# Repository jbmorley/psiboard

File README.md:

# PsiBoard

Psion Series 5 based bluetooth keyboard.

## BOM

### FFC Connector

https://www.digikey.com/en/products/detail/molex/0524372271/3262899

22 Position FFC, FPC Connector Contacts, Bottom 0.020" (0.50mm) Surface Mount, Right Angle

### Reset Switch

https://www.digikey.com/en/products/detail/panasonic-electronic-components/EVQ-P7A01P/4429447

## Development

### Useful Links

- [ZMK Firmware - List of Keycodes](https://zmk.dev/docs/keymaps/list-of-keycodes)
- [ZMK Firmware - Power Management Configuration](https://zmk.dev/docs/config/power)
- [Pro Micro Pinout](https://learn.sparkfun.com/tutorials/pro-micro--fio-v3-hookup-guide/all)

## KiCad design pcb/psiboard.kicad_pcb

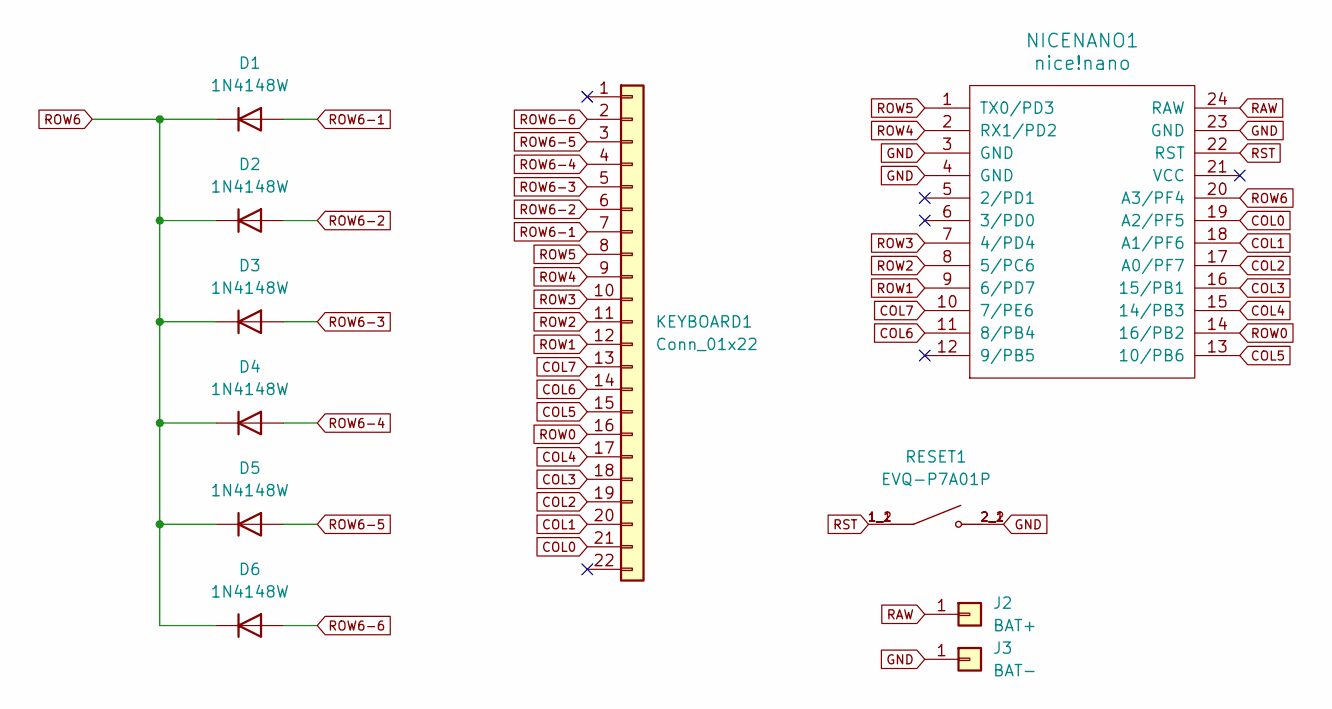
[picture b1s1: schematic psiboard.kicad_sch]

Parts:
D1, D2, D3, D4, D5, D6: 1N4148W; D_SOD-123
J2: BAT+; TestPoint_Pad_2.0x2.0mm
J3: BAT-; TestPoint_Pad_2.0x2.0mm
KEYBOARD1: Conn_01x22; CON_524372271_MOL
NICENANO1: nice!nano
RESET1: EVQ-P7A01P; SW_EVQ-P7A01P; PARTREV 2022.4

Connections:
COL0: KEYBOARD1.21, NICENANO1.19 (A2/PF5)
COL1: KEYBOARD1.20, NICENANO1.18 (A1/PF6)
COL2: KEYBOARD1.19, NICENANO1.17 (A0/PF7)
COL3: KEYBOARD1.18, NICENANO1.16 (15/PB1)
COL4: KEYBOARD1.17, NICENANO1.15 (14/PB3)
COL5: KEYBOARD1.15, NICENANO1.13 (10/PB6)
COL6: KEYBOARD1.14, NICENANO1.11 (8/PB4)
COL7: KEYBOARD1.13, NICENANO1.10 (7/PE6)
GND: J3.1, NICENANO1.3 (GND), NICENANO1.4 (GND), NICENANO1.23 (GND), RESET1.2_1, RESET1.2_2
RAW: J2.1, NICENANO1.24 (RAW)
ROW0: KEYBOARD1.16, NICENANO1.14 (16/PB2)
ROW1: KEYBOARD1.12, NICENANO1.9 (6/PD7)
ROW2: KEYBOARD1.11, NICENANO1.8 (5/PC6)
ROW3: KEYBOARD1.10, NICENANO1.7 (4/PD4)
ROW4: KEYBOARD1.9, NICENANO1.2 (RX1/PD2)
ROW5: KEYBOARD1.8, NICENANO1.1 (TX0/PD3)
ROW6: D1.1 (K), D2.1 (K), D3.1 (K), D4.1 (K), D5.1 (K), D6.1 (K), NICENANO1.20 (A3/PF4)
ROW6-1: D1.2 (A), KEYBOARD1.7
ROW6-2: D2.2 (A), KEYBOARD1.6
ROW6-3: D3.2 (A), KEYBOARD1.5
ROW6-4: D4.2 (A), KEYBOARD1.4
ROW6-5: D5.2 (A), KEYBOARD1.3
ROW6-6: D6.2 (A), KEYBOARD1.2
RST: NICENANO1.22 (RST), RESET1.1_1, RESET1.1_2

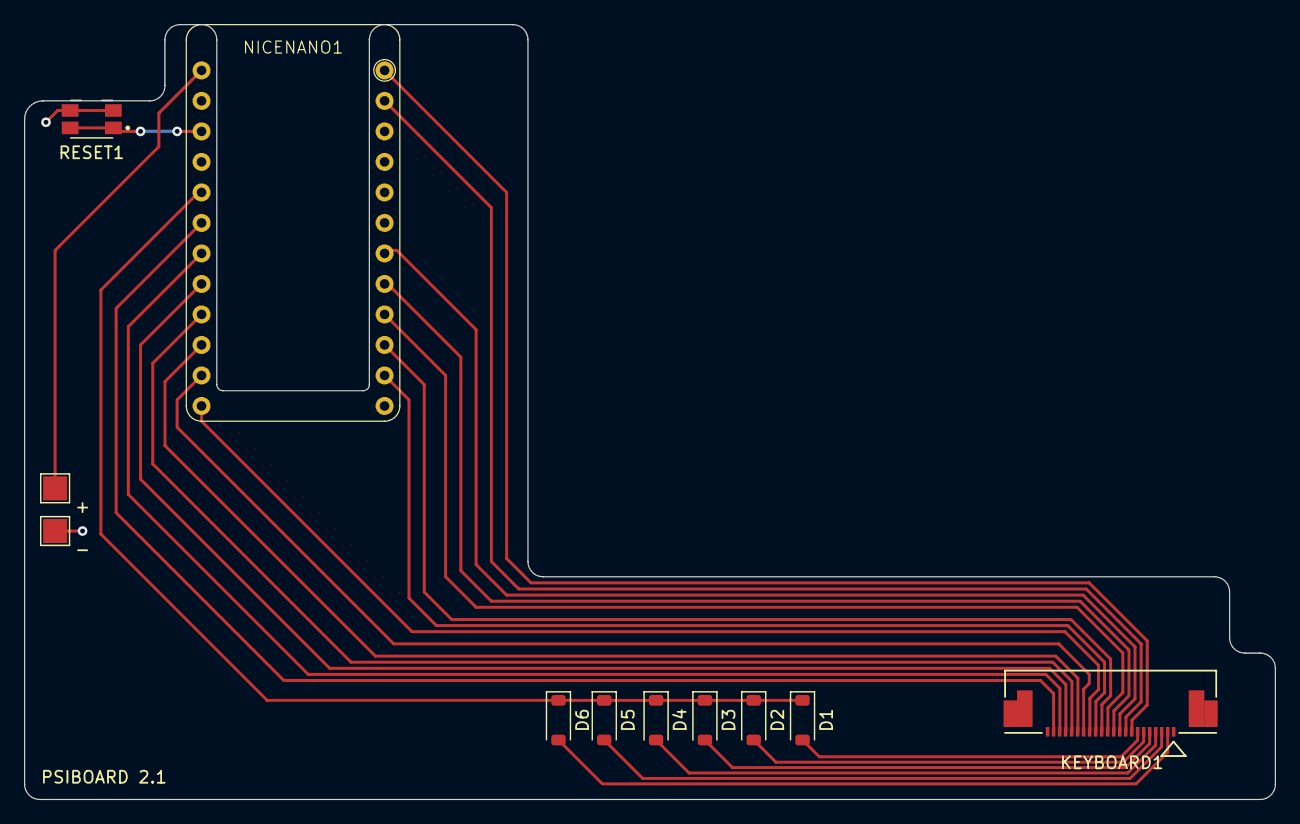
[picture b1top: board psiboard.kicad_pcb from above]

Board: 2 copper layers, 104.1 x 64.5 mm, 11 parts (0 on the bottom side), 24 nets.

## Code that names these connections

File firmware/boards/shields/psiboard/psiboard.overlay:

#include <dt-bindings/zmk/matrix_transform.h>

/ {
    chosen {
        zmk,kscan = &kscan0;
        zmk,matrix_transform = &default_transform;
    };

    keys {
        compatible = "gpio-keys";
        soft_off_gpio_key: soft_off_gpio_key {
            gpios = <&pro_micro 8 (GPIO_ACTIVE_HIGH | GPIO_PULL_DOWN)>;
        };
    };

    soft_off_wakers {
        compatible = "zmk,soft-off-wakeup-sources";
        wakeup-sources = <&wakeup_scan>;
    };

    wakeup_scan: wakeup_scan {
        compatible = "zmk,gpio-key-wakeup-trigger";
        trigger = <&soft_off_gpio_key>;
        wakeup-source;
        extra-gpios = <&pro_micro 21 GPIO_ACTIVE_HIGH>;
    };

    kscan0: kscan_0 {
        compatible = "zmk,kscan-gpio-matrix";
        label = "KSCAN";
        diode-direction = "col2row";

        col-gpios
            = <&pro_micro 20 GPIO_ACTIVE_HIGH>  // COL0 (PM 21 -> KBD 20)
            , <&pro_micro 19 GPIO_ACTIVE_HIGH>  // COL1 (PM 20 -> KBD 19)
            , <&pro_micro 18 GPIO_ACTIVE_HIGH>  // COL2 (PM 19 -> KBD 18)
            , <&pro_micro 15 GPIO_ACTIVE_HIGH>  // COL3 (PM 18 -> KBD 17)
            , <&pro_micro 14 GPIO_ACTIVE_HIGH>  // COL4 (PM 15 -> KBD 16)
            , <&pro_micro 10 GPIO_ACTIVE_HIGH>  // COL5 (PM 14 -> KBD 14)
            , <&pro_micro  8 GPIO_ACTIVE_HIGH>  // COL6 (PM 16 -> KBD 13)
            , <&pro_micro  7 GPIO_ACTIVE_HIGH>  // COL7 (PM 10 -> KBD 12)
            ;

        row-gpios
            = <&pro_micro 16 (GPIO_ACTIVE_HIGH | GPIO_PULL_DOWN)>  // ROW0 (PM 1 -> KBD 15)
            , <&pro_micro  6 (GPIO_ACTIVE_HIGH | GPIO_PULL_DOWN)>  // ROW1 (PM 0 -> KBD 11)
            , <&pro_micro  5 (GPIO_ACTIVE_HIGH | GPIO_PULL_DOWN)>  // ROW2 (PM 4 -> KBD 10)
            , <&pro_micro  4 (GPIO_ACTIVE_HIGH | GPIO_PULL_DOWN)>  // ROW3 (PM 5 -> KBD 9)
            , <&pro_micro  0 (GPIO_ACTIVE_HIGH | GPIO_PULL_DOWN)>  // ROW4 (PM 6 -> KBD 8)
            , <&pro_micro  1 (GPIO_ACTIVE_HIGH | GPIO_PULL_DOWN)>  // ROW5 (PM 7 -> KBD 7)
            , <&pro_micro 21 (GPIO_ACTIVE_HIGH | GPIO_PULL_DOWN)>  // ROW6 (PM 8 -> KBD 1-6)
            ;
    };

    default_transform: matrix_transform {
        compatible = "zmk,matrix-transform";
        columns = <12>;
        rows = <5>;
        // ┌─────┬─────┬─────┬─────┬─────┬─────┬─────┬─────┬─────┬─────┬─────┬─────┐
        // │ Esc │  1  │  2  │  3  │  4  │  5  │  6  │  7  │  8  │  9  │  0  │ Del │
        // └──┬──┴──┬──┴──┬──┴──┬──┴──┬──┴──┬──┴──┬──┴──┬──┴──┬──┴──┬──┴──┬──┴─────┤
        //    │  Q  │  W  │  E  │  R  │  T  │  Y  │  U  │  I  │  O  │  P  │   Ent  │
        // ┌──┴──┬──┴──┬──┴──┬──┴──┬──┴──┬──┴──┬──┴──┬──┴──┬──┴──┬──┴──┬──┴──┐     │
        // │ Tab │  A  │  S  │  D  │  F  │  G  │  H  │  J  │  K  │  L  │ ' ~ │     │
        // └──┬──┴──┬──┴──┬──┴──┬──┴──┬──┴──┬──┴──┬──┴──┬──┴──┬──┴──┬──┴──┬──┴──┬──┘
        //    │ Sft │  Z  │  X  │  C  │  V  │  B  │  N  │  M  │ . ? │ Up  │ Sft │
        //    ├─────┼─────┼─────┼─────┴─────┴─────┴─────┼─────┼─────┼─────┼─────┤
        //    │ Ctl │ Fn  │ Mnu │         Space         │ , / │ Lft │ Dwn │ Rgt │
        //    └─────┴─────┴─────┴───────────────────────┴─────┴─────┴─────┴─────┘
        map = <

        // Esc      1        2        3        4        5        6        7        8        9        0        Del
           RC(6,6)  RC(0,4)  RC(1,4)  RC(2,4)  RC(3,4)  RC(4,4)  RC(5,4)  RC(0,7)  RC(1,7)  RC(2,7)  RC(3,7)  RC(4,7)

        //     Q        W        E        R        T        Y        U        I        O        P        Ent
               RC(0,6)  RC(1,6)  RC(2,6)  RC(3,6)  RC(4,6)  RC(5,6)  RC(0,5)  RC(1,5)  RC(2,5)  RC(3,5)  RC(5,5)

        // Tab      A        S        D        F        G        H        J        K        L        ' ~
           RC(0,3)  RC(1,3)  RC(2,3)  RC(3,3)  RC(4,3)  RC(5,3)  RC(0,2)  RC(1,2)  RC(2,2)  RC(4,5)  RC(5,7)

        //     L. Sft   Z        X        C        V        B        N        M        ?        Up       R. Sft
               RC(6,0)  RC(0,1)  RC(1,1)  RC(2,1)  RC(3,1)  RC(4,1)  RC(5,1)  RC(3,2)  RC(4,2)  RC(2,0)  RC(6,1)

        //     L. Ctl   Fn       Mnu                    Space                 , /      Lft      Dwn      Rgt
               RC(6,3)  RC(6,2)  RC(6,5)                RC(1,0)               RC(3,0)  RC(4,0)  RC(5,2)  RC(5,0)
      >;
    };

};

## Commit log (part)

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2018-02-10 Very first prototype.
    This supports some level of scanning and outputting some key rows.
2018-02-13 General key scanning now works.
2018-02-13 Make keyboard.py executable.
2018-02-14 Fleshing out some of the keys.
2018-02-14 Slightly improved output.
2018-02-14 Storing previous state and emitting key down and key up events.
2018-02-14 Rudimentary shifting support.
2018-02-23 Add the Adafruit hid_keyboard example.
2018-02-23 Some prototype code for interacting with the keyboard.
2018-02-24 Arduino directory structure and lookup table.
2018-02-24 Two columns working.
    Unfortunately this implementation has columns and rows backwards, and should be changed in the future.
2018-02-24 Add some comments.
2018-02-25 Most key events now working.
2018-02-25 Switch over to HID keycodes.
2018-02-25 Rudimentary shifting behaviour and key action.
2018-02-25 Second delay is unnecessary.
2018-02-25 Shift overrides.
2018-02-25 Use KEY_NONE as a re-mappable empty keycode.
2018-02-25 Fn, Menu, and Esc now working.
2018-02-25 Remove one unnecessary row.
2018-02-25 Remove another defunct row.
2018-02-25 Fn key working with the math symbols.
2018-02-25 Fleshing out Fn key behaviour.
2018-02-25 Menu as Command key.
2018-02-28 Cleaner modifier handling.
2018-02-28 Remove unused define.
2018-02-28 Restore the escape key.
    It doesn’t seem to function as I would expect right now.
2018-02-28 Support the control key.
2018-02-28 Using a more appropriate identifier for the Fn key.
2018-02-28 Remove unused variable.
2018-02-28 Update the bluetooth data.
2018-02-28 Slowly cleaning up the code a little.
2018-02-28 Remove the now-legacy serial input support.
2018-03-01 Caps lock.
2018-03-01 More generic modifier event handling.
2018-03-01 Unified modifier handling.
2018-03-02 Switch to using the RX pin (6) instead of DFU for the column.
    This change also required no longer configuring the serial console.
2018-03-04 Initial addition of PCB.
2018-03-04 Basic shape.
2018-03-04 Ignore backup files.
2018-03-04 Add mounting holes.
2018-03-04 Basic board shape.
2018-03-04 Ignore .job files. General shape.
2018-03-04 Add drill holes.
2018-03-05 Rename the firmware file.
2018-03-15 Update eagle version.
2018-03-15 Update pins for the new PCB
    Includes drive-by fix for right shift.
2018-03-15 Disable arrow key modifiers for the time being.
2018-03-25 Initial work on v2 of the PCB.
2018-03-25 Starting to get to the correct board shape.
2018-03-25 Basic board layout now complete, including silkscreen names.
2018-03-25 General board layout improvements.
2018-03-25 General shape now seems correct, as does the silkscreening.
2018-03-25 Schematic is now complete.
2018-03-25 Routing complete.
2018-03-25 Lowercase v for version.
2018-03-25 Remembering to add holes.
2018-03-25 Remove the v1 PCB.
2018-03-25 Add referenced EagleCAD library.
2018-03-25 Add some notes on the changes made to v1.1 of the PCB.
2018-04-07 Add the STL files for the case.
2018-04-07 Update the firmware for the latest PCB.
2018-04-11 Some minor adjustments to the case dimensions
    Includes a first guess at a board mounting height.
2018-04-12 Set up Fusion sync.
2018-07-31 Ignore backup library files.
2018-07-31 Attempting to add a USB-C component.
2018-07-31 Ignore .pro files.
2018-07-31 Remove legacy project file.
2018-07-31 Checking in the first prototype of the USB-C breakout board.
2018-07-31 Add the USB Micro library
2018-07-31 Board design is generally working
2018-07-31 Remove unused USB Micro library.
2018-07-31 Update the board.
2018-07-31 Fix the routing fro the USB.
2018-07-31 Update with Fusion sync.
2018-08-23 Catch the firmware up to PsiBoard v1.2.
2018-09-07 Add images.
2021-02-17 Create LICENSE
2021-02-17 Add an export of the Fusion 360 models.
    The dimensions of these aren't quite right at the moment, but they're intended to help others get started while the project is idle.
2024-05-26 Add more ideas and sketches
2025-10-06 Add the keyboard membrane reference scans
2025-10-06 Move the PCB into the v1 directory
2025-10-06 Update the hero image
2025-10-06 Move reference sketches
2025-10-07 Remove legacy breakout board
2025-10-07 Remove proof-of-concept Raspberry Pi polling scripts
2025-10-07 Move the legacy Fusion 360 case designs into `v1`
2025-10-07 Move the legacy STL exports into the v1 folder
2025-10-07 Remove legacy tasks from the readme
2025-10-07 Move the legacy firmware into the `v1` directory
2025-10-07 Move the legacy Eagle component libraries into `v1/pcb`
2025-10-07 Add the nice!nano version of the PCB
2025-10-07 Remove unnecessary files
2025-10-07 Remove exported step file
2025-10-07 Rename the pcb project
2025-10-07 Update gitignore
2025-10-07 Add the nice!nano version of the PCB (#2)
2025-10-07 Add the ZMK firmware
2025-10-07 Rename the firmware directory
2025-10-07 Add the ZMK firmware (#3)
2025-10-07 Rename the workflow file
2025-10-07 Rename the workflow file (#4)
2025-10-07 Reanme the workflow and firmware build job
2025-10-07 docs: Add a GitHub Actions workflow status badge
2025-10-07 docs: Add a GitHub Actions workflow status badge (#6)
2025-10-07 Rename the workflow and firmware build job (#5)
2025-10-07 docs: Add a full stop after the description
2025-10-07 docs: Add a full stop after the description (#7)
2025-10-11 fix: Remove unnecessary NC scanning row
2025-10-11 Switch rows 1 and 2 to test things
2025-10-11 Change the delays
2025-10-11 Switch the columns this time and see if thigns move
2025-10-11 Active low instead?
2025-10-11 Go back to the original layout
2025-10-12 Simplify things
2025-10-12 fix(firmware): Remove unnecessary scanning row (#8)
2025-10-12 Hand-route keyboard to simplify layout
2025-10-12 Latest iteration
2025-10-12 Add components to readme
2025-10-12 Add ground plane
2025-10-12 Ignore auto-generated archives
2025-10-14 Update the firmware to match the new PCB layout
2025-10-14 Increase the PCB size to leave room for a status LED
2025-10-14 Final versions
2025-10-14 fix(pcb): Hand-route keyboard to simplify layout (#9)
    This change also introduces a ground plane and makes the PCB
    significantly larger to allow placement of a status LED in future
    iterations.
2025-10-14 chore(pcb): Ignore autosave files
2025-10-14 chore(pcb): Ignore autosave files (#10)
2025-10-25 chore: Add nice!nano reference model and pinout
2025-10-26 chore: Add nice!nano reference model and pinout (#11)
2025-10-26 feat: Add the first-cut manufacturing exports
2025-10-26 feat: Add the first-cut manufacturing exports (#12)
2025-11-08 fix(firmware): Update the wakeup source pinout
2025-12-02 docs: Add some useful references to the readme
    Added development section with useful links.
2025-12-02 docs: Add some useful references to the readme (#20)
    Added development section with useful links.
